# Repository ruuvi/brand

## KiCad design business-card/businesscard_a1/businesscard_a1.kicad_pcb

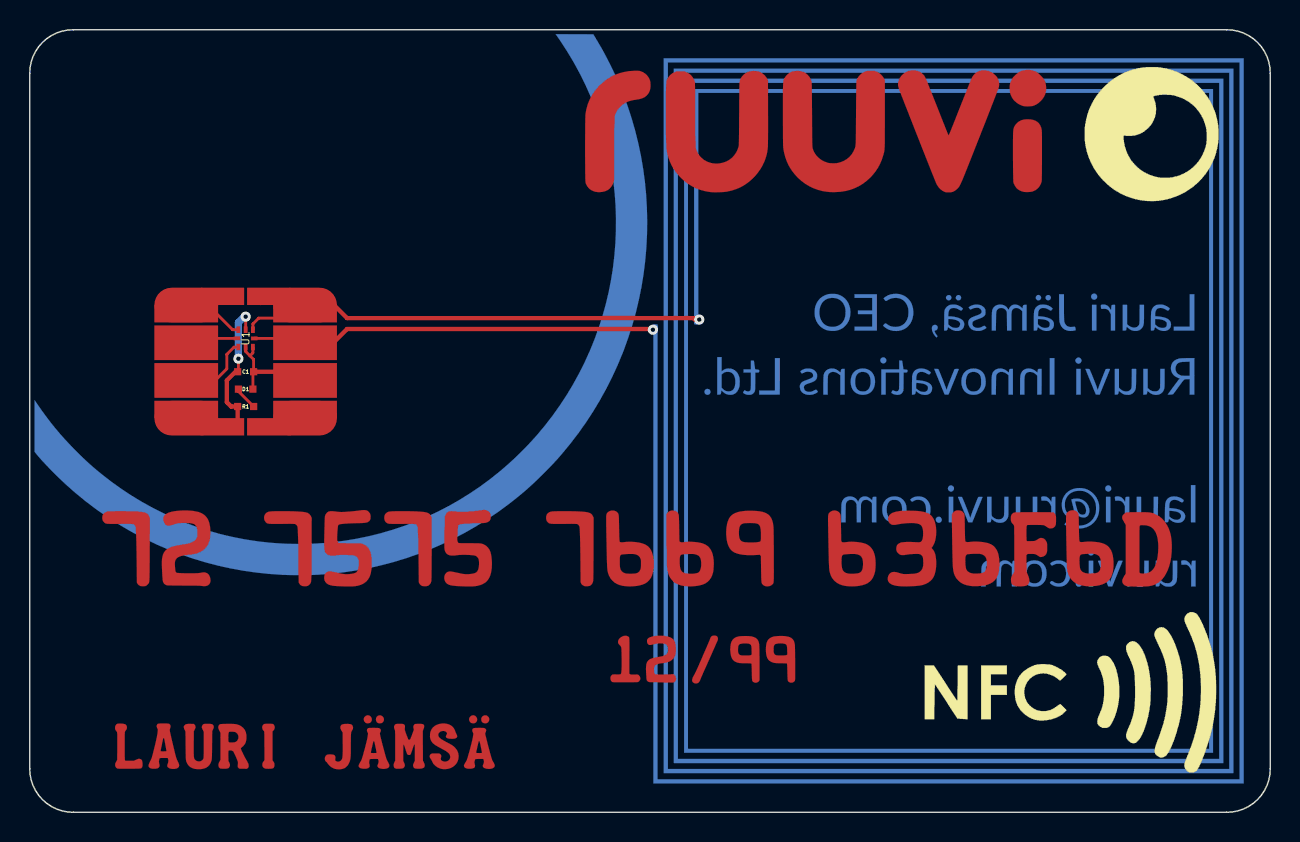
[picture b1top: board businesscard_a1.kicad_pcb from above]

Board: 2 copper layers, 85.6 x 54.0 mm, 6 parts (1 on the bottom side), 8 nets.

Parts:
C1: 220n; 0402_CAP
D1: LED; 0402_LED
P1: NFC; BUSINESS_NFC_ANTENNA_4X5CM_NEW
P2: CREDIT_CARD; CREDIT_CARD_CHIP_EMPTY
R1: 470; 0402_RES
U1: NTAG_NT3H1X01; SOT902-3

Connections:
/FIELD: P2.C2, U1.4
/LA: P1.2, P2.C5, U1.1
/LB: P1.1, P2.C6, U1.8
/SCL: P2.C1, U1.3
/SDA: P2.C3, U1.5
GND: C1.2, P2.C4, R1.2, U1.2
unnamed: D1.1, R1.1
VDD: C1.1, D1.2, P2.C7, U1.6, U1.7

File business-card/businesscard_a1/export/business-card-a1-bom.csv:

Id,Designator,Package,Quantity,Designation,Manufacturer and part no.
1,R1,0402_RES,1,470,General min 5% 0402 resistor
2,D1,0402_LED,1,LED,Vishay Semiconductor Opto Division VLMO1500-GS08
3,C1,0402_CAP,1,220n,General min 20% 10V 0402 capacitor
4,U1,SOT902-3,1,NTAG_NT3H1X01,NXP Semiconductors NT3H1201W0FHK

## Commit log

2015-12-02 Logo initial commit
2015-12-02 Factsheet initial commit
2015-12-02 New folder
2015-12-02 Add low res .jpg
2015-12-03 Dome decal
2015-12-04 Add new image
2015-12-04 PNG export 2000dpi 35mm
2015-12-04 Stroke to path
2015-12-04 CMYK 80% black
2015-12-04 CMYK
2015-12-06 Small fixes end pdf exports
2015-12-07 Add version with lighter text (70% instead of 75%)
2015-12-07 Fix white background of eye
2015-12-07 Rename
2015-12-11 Bolder circle and darker text for doming progress
2015-12-11 Move
2016-01-25 Update image and add a mention about NFC
2016-01-25 Add lowres JPG
2016-01-25 Add OSHW logo
2016-01-25 Add NFC antenna
2016-01-25 Fix copper
2016-01-25 Reconnect chip
2016-01-25 More space to middle
2016-01-26 Fix silk
2016-01-26 New NFC antenna
2016-01-26 Update data sheet
2016-01-26 Small mods
2016-01-26 Plot gerbers
2016-01-26 Add BOM
2016-01-26 Add ready
2016-01-26 Plots
2016-01-26 Plot
2016-01-26 Minor mods
2016-01-26 Add pic
2016-01-26 Add test instructions
2016-01-26 Add assembly pics
2016-01-26 Typo fix
2016-01-26 Better images
2016-01-28 Add copper into the eye
2016-01-28 New plot
2016-01-28 Update led's 3d model
2016-01-28 Update images
2016-01-29 New pics
2016-01-29 Add Slack image
2016-01-29 Update ready
2016-01-29 Add screenshot pdf
2016-01-29 Texts to paths
2016-01-29 Add more canvas
2016-04-14 Darker text
2016-04-14 Add read
2016-04-15 Fix filter
2016-04-18 Add Thai translation
2016-04-18 Minor fix
2016-04-18 Add new pics
2016-04-18 New pic
2016-04-18 Add 3D pic
2016-04-18 New 3D pic
2016-04-18 Update specs
2016-04-18 Small fix
2016-04-18 Add photo path
2016-04-18 Fix path
2016-04-18 Smaller icons
2016-04-19 Reorganize
2016-04-19 Add PNG
2016-04-20 Add corner image
2016-04-20 New image
2016-04-20 Remove logo
2016-04-20 Add SVG
2016-04-29 Add 16:9 version
2016-06-06 Company card
2016-06-06 Update EN press release
2016-06-06 Flyer frontpage
2016-06-06 Doubleraster PDF
2016-06-06 New high res image
2016-06-06 PCBnew image
2016-06-26 Added a reversed white logo. 2-color reversed logo Round eye size reduced as already done in the press releases.
2016-06-27 Revert changes made on the original logo. The white background is required.
2017-02-13 Update (90% CMYK)
2017-02-13 Edit
2017-10-29 Update text
2017-11-06 Add eye version without edges
2017-12-15 Add nega logo
